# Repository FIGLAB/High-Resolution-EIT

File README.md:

# High-Resolution-EIT

The high resolution Electrical Impedance Tomograph (EIT) project is provided for academic and non-commercial research. This project is based on our publication at ACM UIST 2016: https://dl.acm.org/doi/abs/10.1145/2984511.2984574

## ACM Ref

Yang Zhang, Robert Xiao, and Chris Harrison. 2016. Advancing Hand Gesture Recognition with High Resolution Electrical Impedance Tomography. In Proceedings of the 29th Annual Symposium on User Interface Software and Technology (UIST '16). Association for Computing Machinery, New York, NY, USA, 843–850. DOI:https://doi.org/10.1145/2984511.2984574

## BibTex

```
@inproceedings{10.1145/2984511.2984574,
author = {Zhang, Yang and Xiao, Robert and Harrison, Chris},
title = {Advancing Hand Gesture Recognition with High Resolution Electrical Impedance Tomography},
year = {2016},
isbn = {9781450341899},
publisher = {Association for Computing Machinery},
address = {New York, NY, USA},
url = {https://doi.org/10.1145/2984511.2984574},
doi = {10.1145/2984511.2984574},
abstract = {Electrical Impedance Tomography (EIT) was recently employed in the HCI domain to detect hand gestures using an instrumented smartwatch. This prior work demonstrated great promise for non-invasive, high accuracy recognition of gestures for interactive control. We introduce a new system that offers improved sampling speed and resolution. In turn, this enables superior interior reconstruction and gesture recognition. More importantly, we use our new system as a vehicle for experimentation ' we compare two EIT sensing methods and three different electrode resolutions. Results from in-depth empirical evaluations and a user study shed light on the future feasibility of EIT for sensing human input.},
booktitle = {Proceedings of the 29th Annual Symposium on User Interface Software and Technology},
pages = {843–850},
numpages = {8},
keywords = {hand gestures, eit, electrical impedance tomography, biometrics, smartwatch, bio-impedance, input},
location = {Tokyo, Japan},
series = {UIST '16}
}
```

## Contact

For interests in commercialization, please reach out to CMU CTTEC for details at innovation@cmu.edu

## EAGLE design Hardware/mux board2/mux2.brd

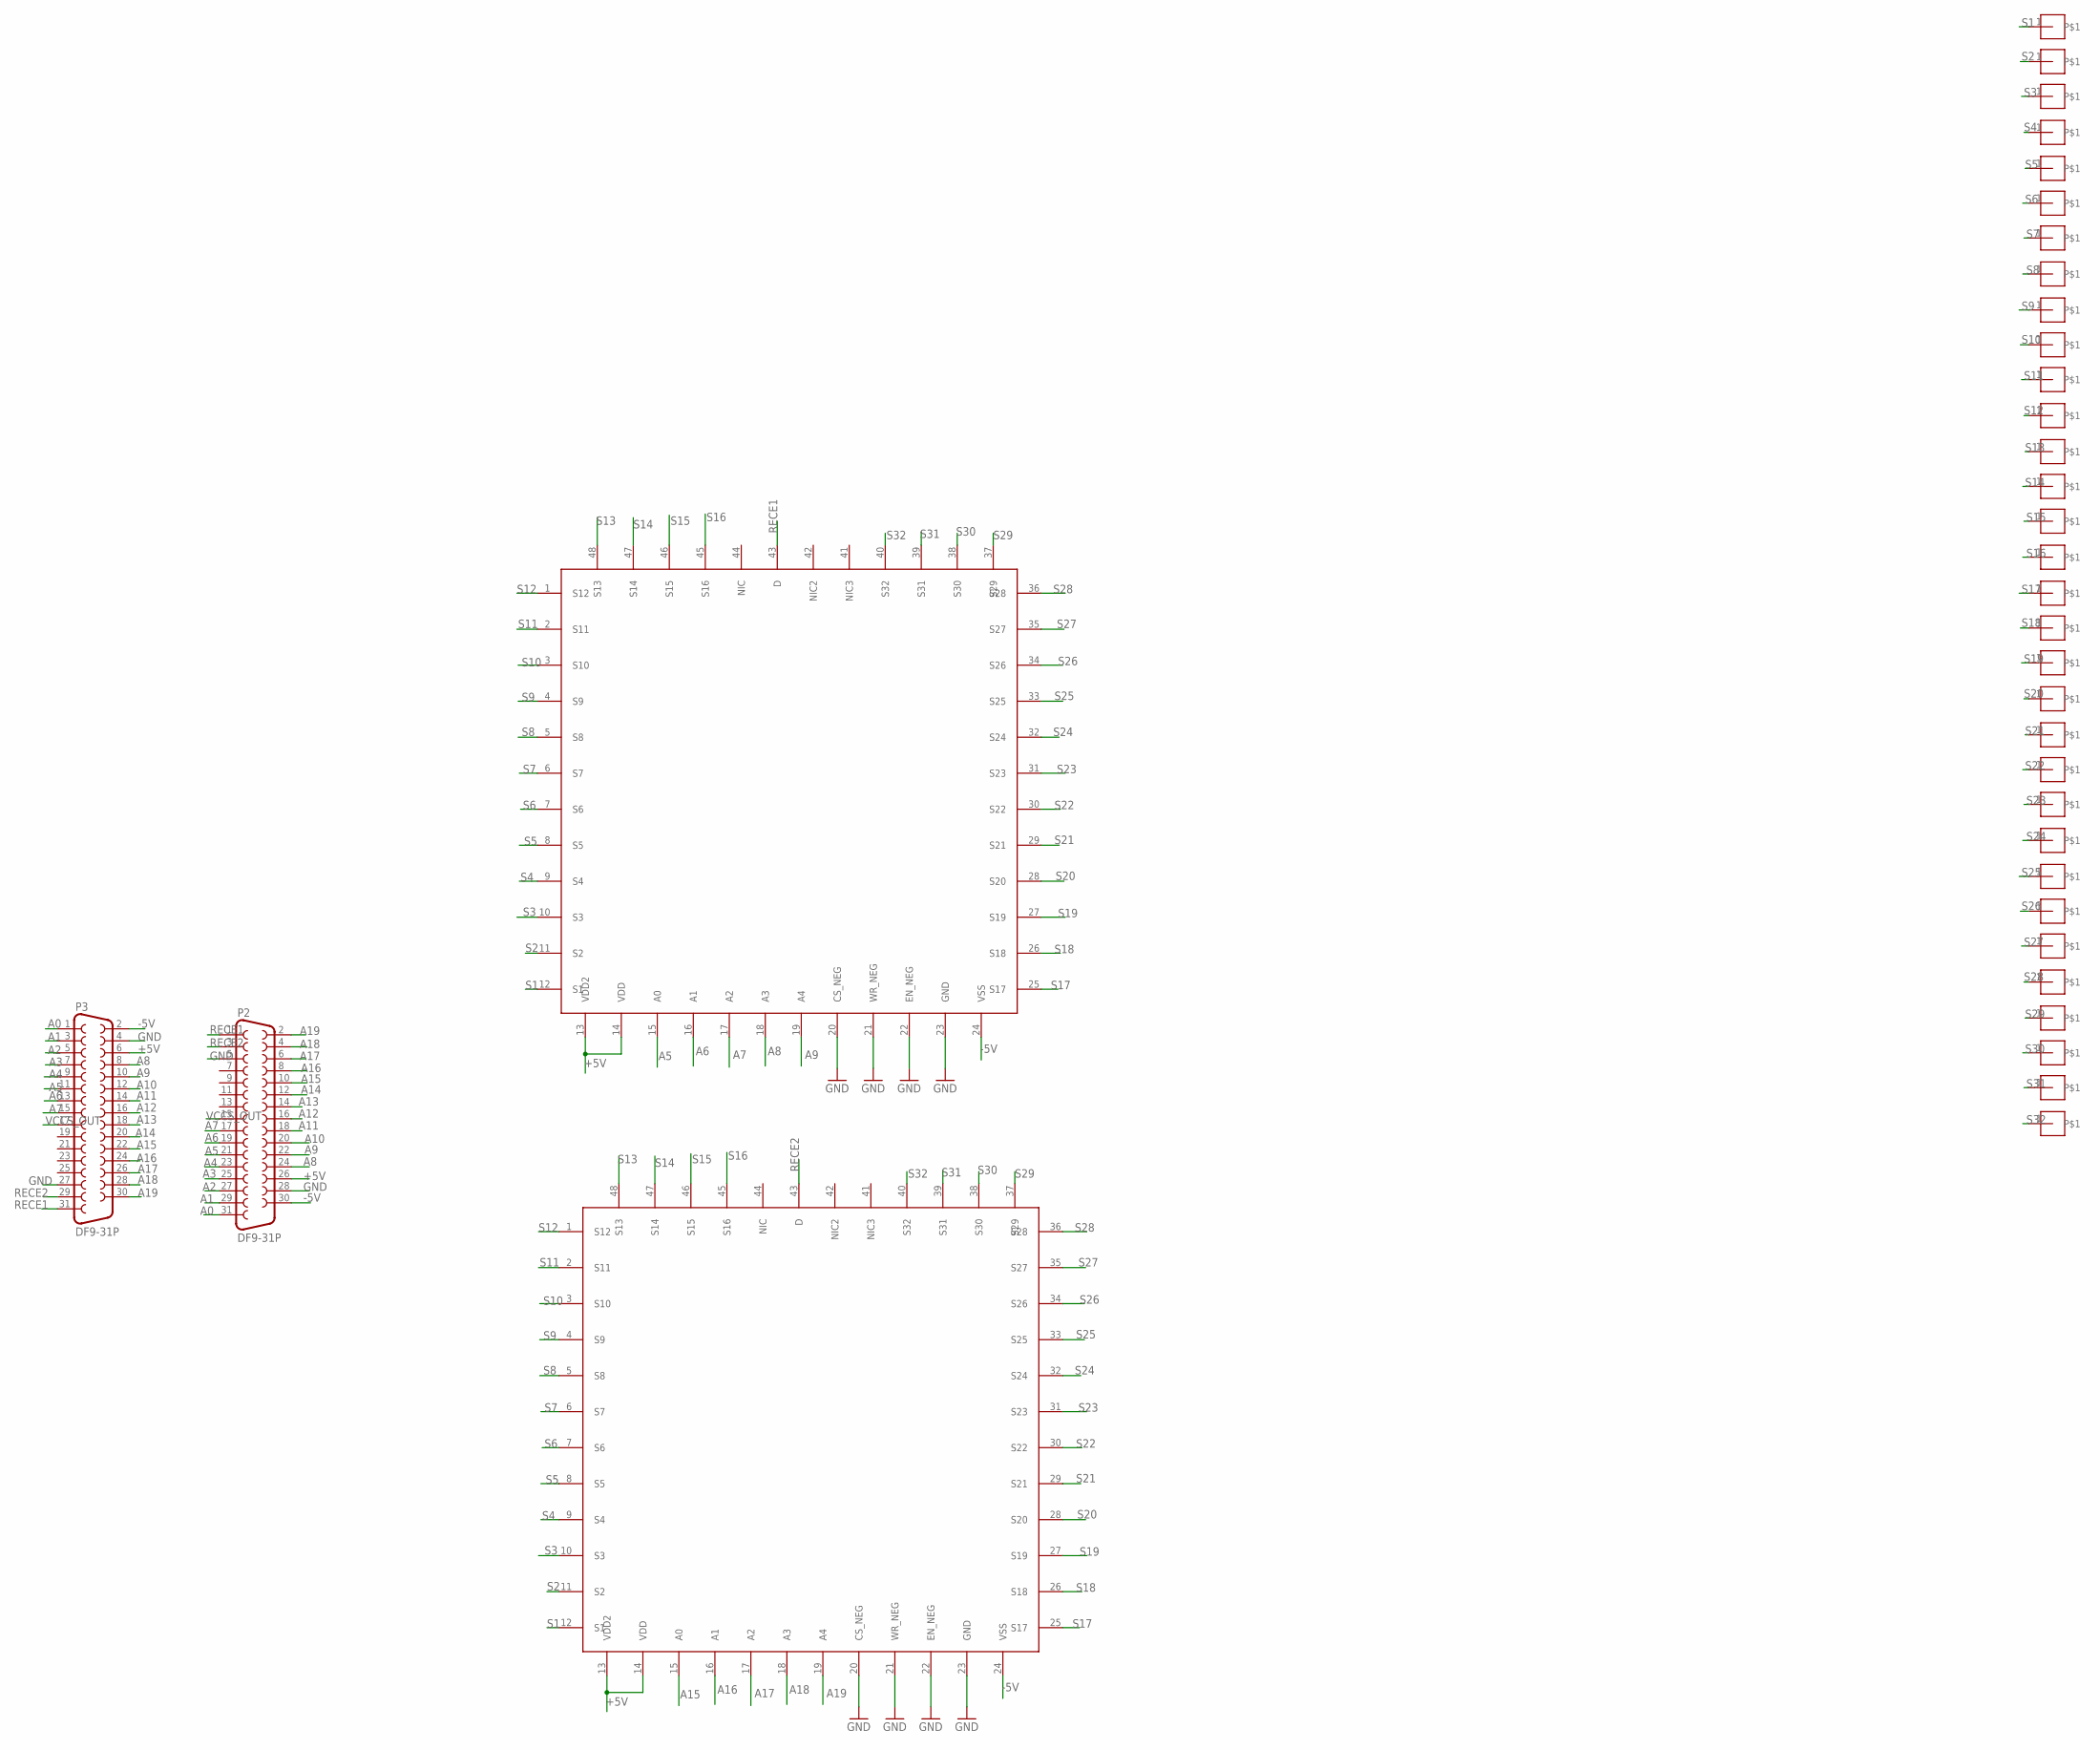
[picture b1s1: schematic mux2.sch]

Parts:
P2, P3: DF9-31P
U$25, U$26, U$27, U$28, U$29, U$30, U$31, U$32, U$33, U$34, U$35, U$36, U$37, U$38, U$39, U$40, U$41, U$42, U$43, U$44, U$45, U$46, U$47, U$48, U$49, U$50, U$51, U$52, U$53, U$54, U$55, U$56: M01
U$73, U$74: ADG732; TQFP48

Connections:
+5V: P2.26, P3.6, U$73.13 (VDD2), U$73.14 (VDD), U$74.13 (VDD2), U$74.14 (VDD)
-5V: P2.30, P3.2, U$73.24 (VSS), U$74.24 (VSS)
A0: P2.31, P3.1
A1: P2.29, P3.3
A2: P2.27, P3.5
A3: P2.25, P3.7
A4: P2.23, P3.9
A5: P2.21, P3.11, U$74.15 (A0)
A6: P2.19, P3.13, U$74.16 (A1)
A7: P2.17, P3.15, U$74.17 (A2)
A8: P2.24, P3.8, U$74.18 (A3)
A9: P2.22, P3.10, U$74.19 (A4)
A10: P2.20, P3.12
A11: P2.18, P3.14
A12: P2.16, P3.16
A13: P2.14, P3.18
A14: P2.12, P3.20
A15: P2.10, P3.22, U$73.15 (A0)
A16: P2.8, P3.24, U$73.16 (A1)
A17: P2.6, P3.26, U$73.17 (A2)
A18: P2.4, P3.28, U$73.18 (A3)
A19: P2.2, P3.30, U$73.19 (A4)
GND: P2.5, P2.28, P3.4, P3.27, U$73.20 (CS_NEG), U$73.21 (WR_NEG), U$73.22 (EN_NEG), U$73.23 (GND), U$74.20 (CS_NEG), U$74.21 (WR_NEG), U$74.22 (EN_NEG), U$74.23 (GND)
RECE1: P2.1, P3.31, U$74.43 (D)
RECE2: P2.3, P3.29, U$73.43 (D)
S1: U$25.1, U$73.12 (S1), U$74.12 (S1)
S2: U$26.1, U$73.11 (S2), U$74.11 (S2)
S3: U$27.1, U$73.10 (S3), U$74.10 (S3)
S4: U$28.1, U$73.9 (S4), U$74.9 (S4)
S5: U$29.1, U$73.8 (S5), U$74.8 (S5)
S6: U$30.1, U$73.7 (S6), U$74.7 (S6)
S7: U$31.1, U$73.6 (S7), U$74.6 (S7)
S8: U$32.1, U$73.5 (S8), U$74.5 (S8)
S9: U$33.1, U$73.4 (S9), U$74.4 (S9)
S10: U$34.1, U$73.3 (S10), U$74.3 (S10)
S11: U$35.1, U$73.2 (S11), U$74.2 (S11)
S12: U$36.1, U$73.1 (S12), U$74.1 (S12)
S13: U$37.1, U$73.48 (S13), U$74.48 (S13)
S14: U$38.1, U$73.47 (S14), U$74.47 (S14)
S15: U$39.1, U$73.46 (S15), U$74.46 (S15)
S16: U$40.1, U$73.45 (S16), U$74.45 (S16)
S17: U$41.1, U$73.25 (S17), U$74.25 (S17)
S18: U$42.1, U$73.26 (S18), U$74.26 (S18)
S19: U$43.1, U$73.27 (S19), U$74.27 (S19)
S20: U$44.1, U$73.28 (S20), U$74.28 (S20)
S21: U$45.1, U$73.29 (S21), U$74.29 (S21)
S22: U$46.1, U$73.30 (S22), U$74.30 (S22)
S23: U$47.1, U$73.31 (S23), U$74.31 (S23)
S24: U$48.1, U$73.32 (S24), U$74.32 (S24)
S25: U$49.1, U$73.33 (S25), U$74.33 (S25)
S26: U$50.1, U$73.34 (S26), U$74.34 (S26)
S27: U$51.1, U$73.35 (S27), U$74.35 (S27)
S28: U$52.1, U$73.36 (S28), U$74.36 (S28)
S29: U$53.1, U$73.37 (S29), U$74.37 (S29)
S30: U$54.1, U$73.38 (S30), U$74.38 (S30)
S31: U$55.1, U$73.39 (S31), U$74.39 (S31)
S32: U$56.1, U$73.40 (S32), U$74.40 (S32)
VCCS_OUT: P2.15, P3.17

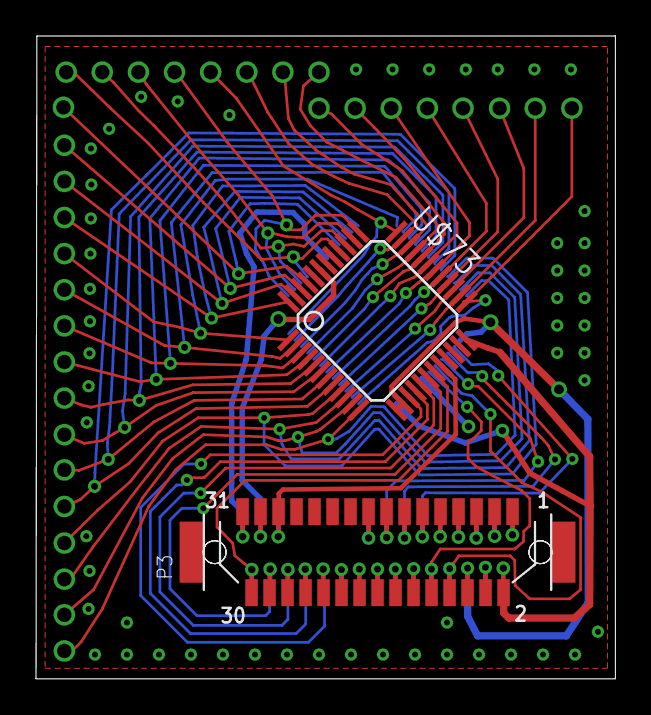
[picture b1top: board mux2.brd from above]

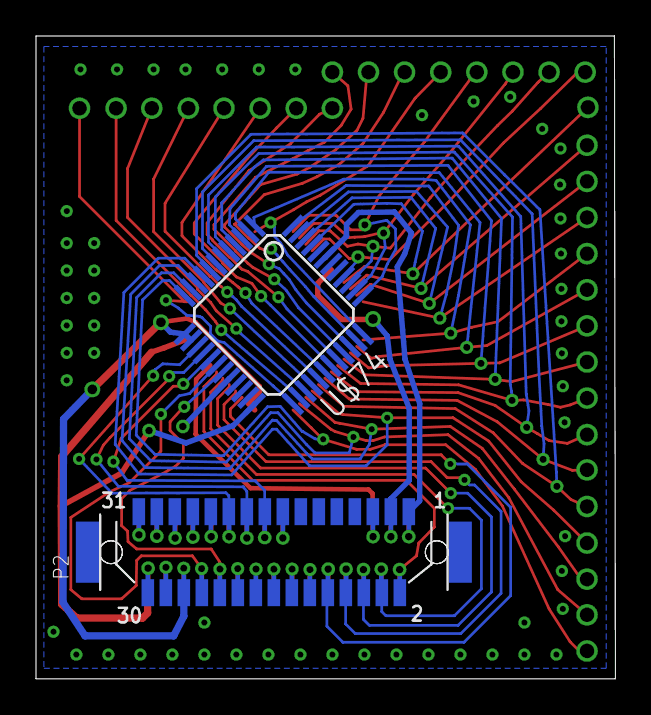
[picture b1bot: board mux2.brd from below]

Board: 2 copper layers, 32.2 x 35.7 mm, 36 parts (2 on the bottom side), 58 nets.

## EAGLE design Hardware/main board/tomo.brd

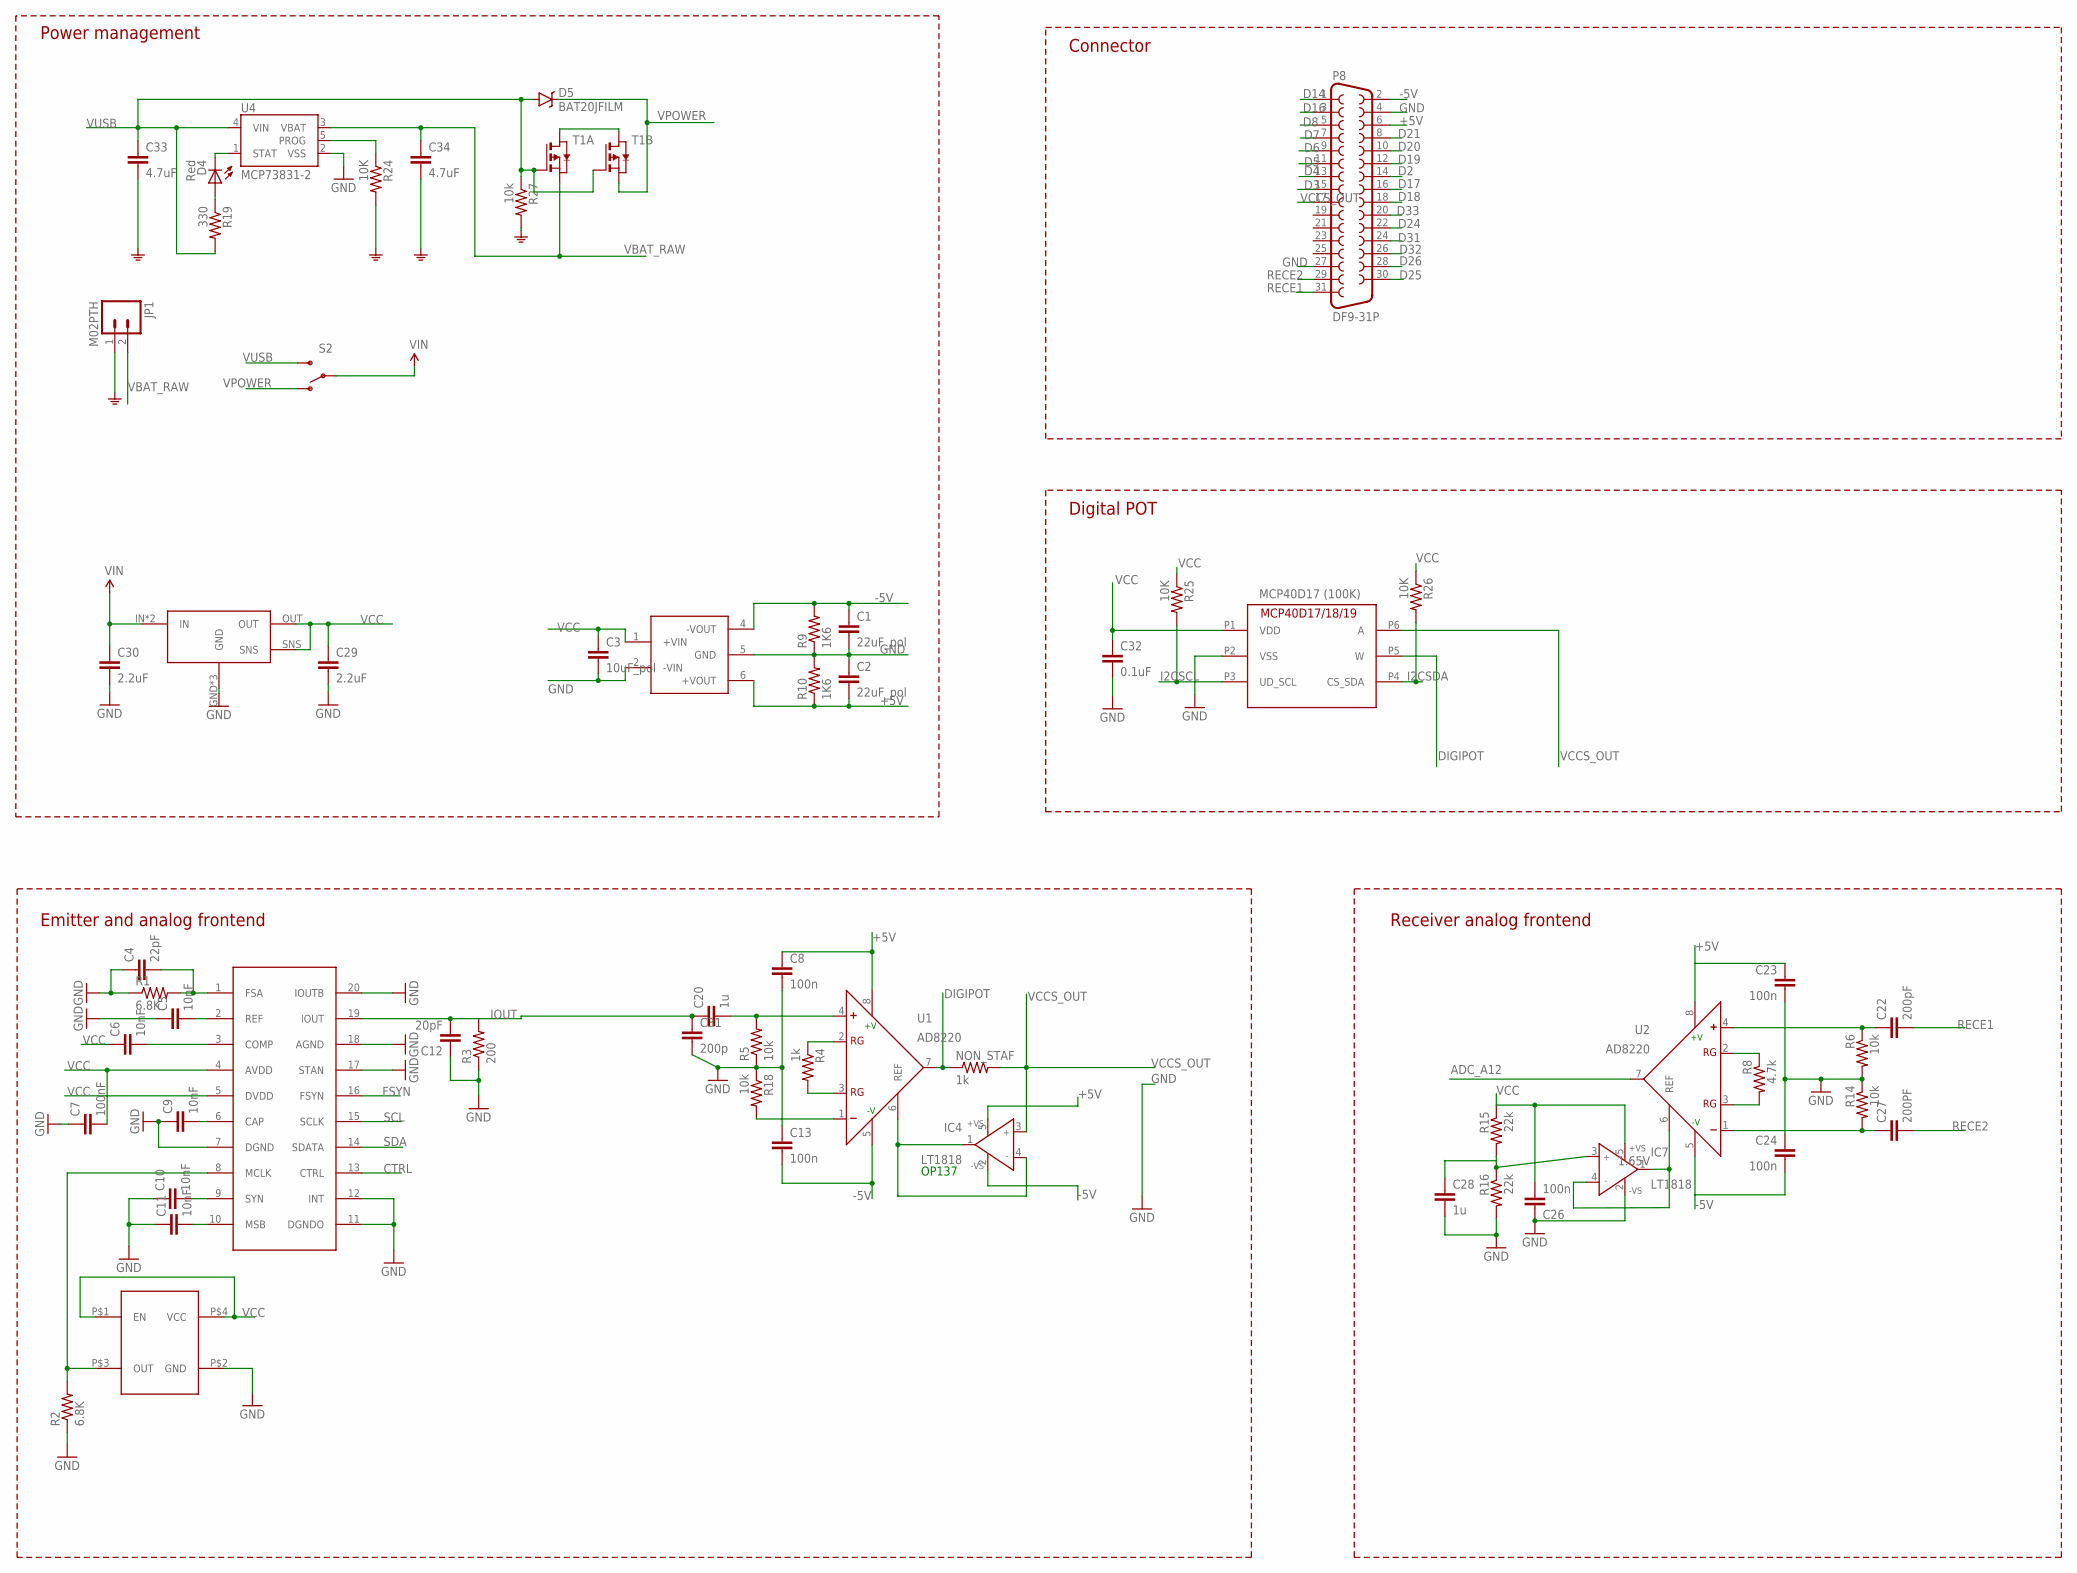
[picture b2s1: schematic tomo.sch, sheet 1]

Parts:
C1, C2: 22uF_pol; 0603-CAP
C3: 10uF_pol; 0603-CAP
C4: 22pF; 0603-CAP
C5, C6, C9, C10, C11: 10nF; 0603-CAP
C7: 100nF; 0603-CAP
C8, C13, C23, C24, C26: 100n; 0603-CAP
C12: 20pF; 0603-CAP
C20, C28: 1u; 0603-CAP
C22: 200pF; 0603-CAP
C27: 200PF; 0603-CAP
C29, C30: 2.2uF; 0402-CAP
C31: 200p; 0603-CAP
C32: 0.1uF; 0402-CAP
C33, C34: 4.7uF; 0402-CAP
D4: Red; LED-0603
D5: BAT20JFILM; SOD-323
IC4, IC7: LT1818; SOT23-5
JP1: M02PTH; 1X02
LP1: LP38691SD; WSON_6
NON_STAF: 1k; 0603-RES
P8: DF9-31P
R1, R2: 6.8K; 0603
R3: 200; 0603
R4: 1k; 0603-RES
R5, R18: 10k; 0603-RES
R6, R14: 10k; 0603
R8: 4.7k; 0603
R9, R10: 1K6; 0603-RES
R15, R16: 22k; 0603
R19: 330; 0402-RES
R24, R25, R26: 10K; 0402-RES
R27: 10k; 0402-RES
S2: SWITCH-SPDT-SMD-A; SWITCH-SPST-SMD-A
T1: BSS84DW; SOT363
U1, U2: AD8220; MSOP8
U4: MCP73831-2; SOT23-5
U$2: AD5930; TSSOP-20
U$3: OSC
U$4: DCDC_CONVERTOR
U$6: MCP40D17/18/19; SC70-6

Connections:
1.65V: IC7.1 (OUT), IC7.4 (IN-), U2.6 (REF)
+5V: C2.2, C8.1, C23.1, IC4.5 (+VS), P8.6, R10.1, U1.8 (+V), U2.8 (+V), U$4.6 (+VOUT)
-5V: C1.1, C13.2, C24.2, IC4.2 (-VS), P8.2, R9.2, U1.5 (-V), U2.5 (-V), U$4.4 (-VOUT)
ADC_A12: U2.7 (OUT); also elsewhere on the board
CTRL: U$2.13 (CTRL); also elsewhere on the board
D2: P8.14; also elsewhere on the board
D3: P8.15; also elsewhere on the board
D4: P8.13; also elsewhere on the board
D5: P8.11; also elsewhere on the board
D6: P8.9; also elsewhere on the board
D7: P8.7; also elsewhere on the board
D8: P8.5; also elsewhere on the board
D14: P8.1; also elsewhere on the board
D16: P8.3; also elsewhere on the board
D17: P8.16; also elsewhere on the board
D18: P8.18; also elsewhere on the board
D19: P8.12; also elsewhere on the board
D20: P8.10; also elsewhere on the board
D21: P8.8; also elsewhere on the board
D24: P8.22; also elsewhere on the board
D25: P8.30; also elsewhere on the board
D26: P8.28; also elsewhere on the board
D31: P8.24; also elsewhere on the board
D32: P8.26; also elsewhere on the board
D33: P8.20; also elsewhere on the board
DIGIPOT: NON_STAF.1, U1.7 (OUT), U$6.P5 (W)
FSYN: U$2.16 (FSYN); also elsewhere on the board
GND: C1.2, C2.1, C3.2, C4.1, C5.1, C7.1, C8.2, C9.1, C10.1, C11.1, C12.1, C13.1, C23.2, C24.1, C26.1, C28.2, C29.2, C30.2, C31.2, C32.2, C33.2, C34.2, IC7.2 (-VS), JP1.1, LP1.GND, LP1.N/C (GND), LP1.THERMAL (GND), P8.4, P8.27, R1.1, R2.1, R3.1, R5.1, R6.2, R9.1, R10.2, R14.1, R16.2, R18.1, R24.2, R27.2, U4.2 (VSS), U$2.7 (DGND), U$2.11 (DGNDO), U$2.12 (INT), U$2.17 (STAN), U$2.18 (AGND), U$2.20 (IOUTB), U$3.P$2 (GND), U$4.2 (-VIN), U$4.5 (GND), U$6.P2 (VSS); also elsewhere on the board
I2CSCL: R25.2, U$6.P3 (UD_SCL); also elsewhere on the board
I2CSDA: R26.2, U$6.P4 (CS_SDA); also elsewhere on the board
IOUT: C12.2, C20.1, C31.1, R3.2, U$2.19 (IOUT)
unnamed: C4.2, R1.2, U$2.1 (FSA)
unnamed: C6.2, U$2.3 (COMP)
unnamed: C5.2, U$2.2 (REF)
unnamed: C9.2, U$2.6 (CAP)
unnamed: R2.2, U$2.8 (MCLK), U$3.P$3 (OUT)
unnamed: C10.2, U$2.9 (SYN)
unnamed: C11.2, U$2.10 (MSB)
unnamed: R4.1, U1.2 (RG)
unnamed: C28.1, IC7.3 (IN+), R15.2, R16.1
unnamed: C20.2, R5.2, U1.4 (+)
unnamed: R4.2, U1.3 (RG)
unnamed: IC4.1 (OUT), IC4.4 (IN-), U1.6 (REF)
unnamed: R18.2, U1.1 (-)
unnamed: D4.A, R19.1
unnamed: T1.3 (D), T1.6 (D)
unnamed: C22.1, R6.1, U2.4 (+)
unnamed: C27.1, R14.2, U2.1 (-)
unnamed: R8.1, U2.2 (RG)
unnamed: R8.2, U2.3 (RG)
PROG: R24.1, U4.5 (PROG)
RECE1: C22.2, P8.31
RECE2: C27.2, P8.29
SCL: U$2.15 (SCLK); also elsewhere on the board
SDA: U$2.14 (SDATA); also elsewhere on the board
STAT: D4.C, U4.1 (STAT)
VBAT_RAW: C34.1, JP1.2, T1.4 (S), U4.3 (VBAT)
VCC: C3.1, C6.1, C7.2, C26.2, C29.1, C32.1, IC7.5 (+VS), LP1.OUT, LP1.SNS, R15.1, R25.1, R26.1, U$2.4 (AVDD), U$2.5 (DVDD), U$3.P$1 (EN), U$3.P$4 (VCC), U$4.1 (+VIN), U$6.P1 (VDD)
VCCS_OUT: IC4.3 (IN+), NON_STAF.2, P8.17, U$6.P6 (A)
VIN: C30.1, LP1.IN, LP1.IN2 (IN), S2.2; also elsewhere on the board
VPOWER: D5.C, S2.1 (O), T1.1 (S)
VUSB: C33.1, D5.A, R19.2, R27.1, S2.3 (S), T1.2 (G), T1.5 (G), U4.4 (VIN); also elsewhere on the board

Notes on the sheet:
OP137
MCP40D17 (100K)
Power management
Connector
Digital POT
Emitter and analog frontend
Receiver analog frontend

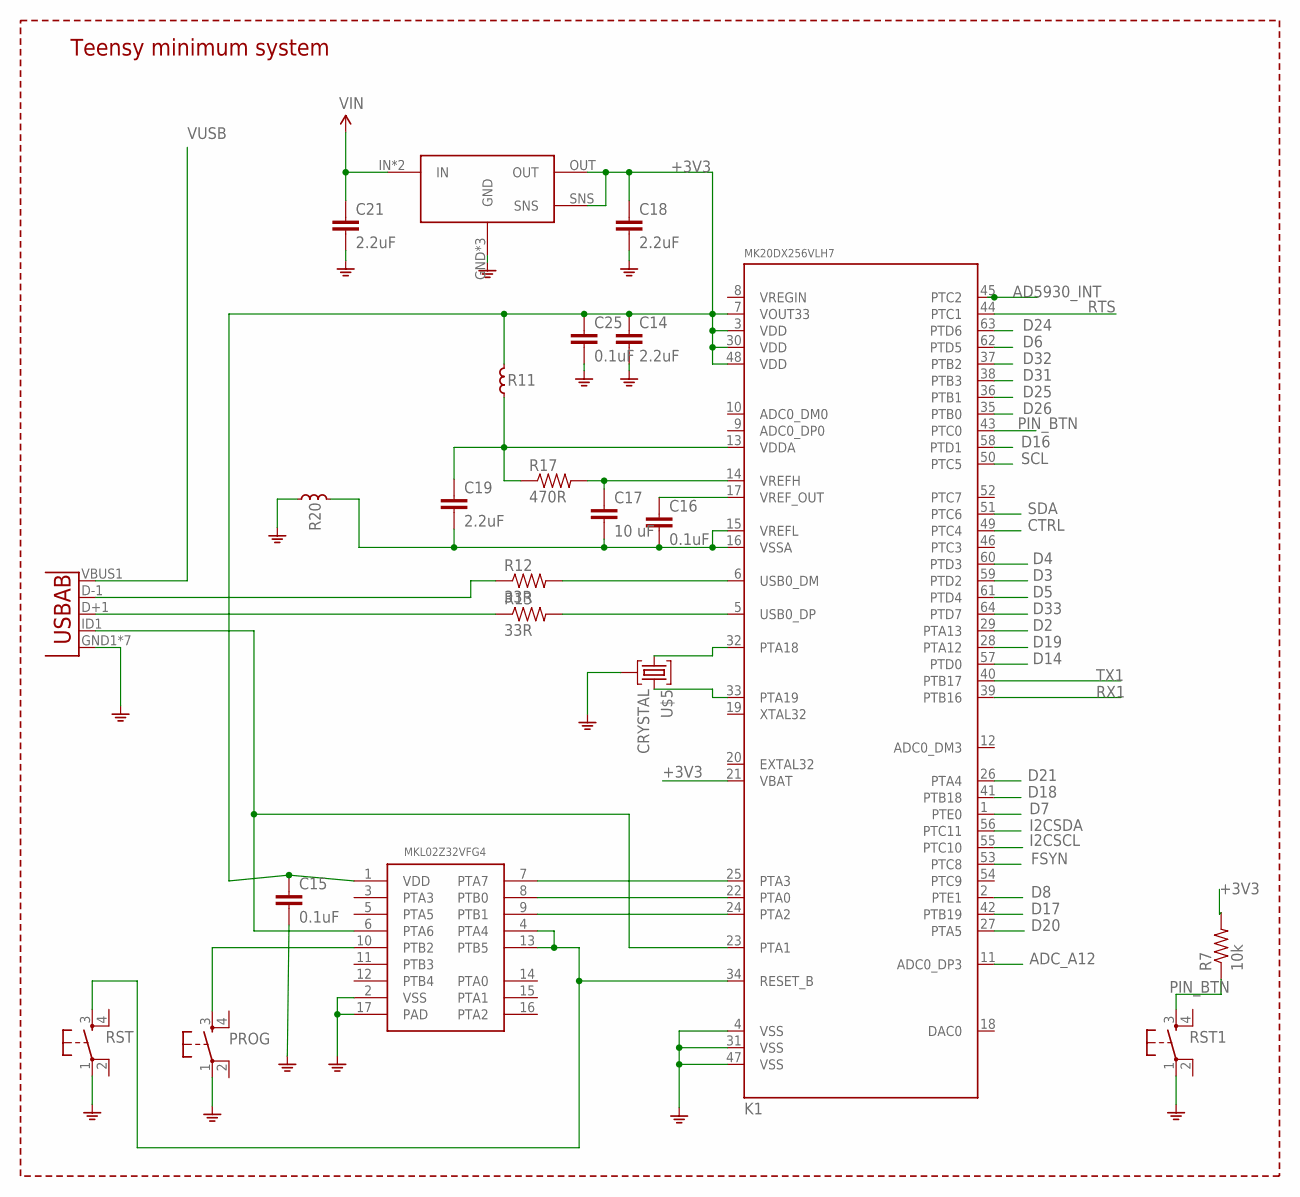
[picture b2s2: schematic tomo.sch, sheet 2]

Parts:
C14: 2.2uF; 0603-CAP
C15, C16, C25: 0.1uF; 0402-CAP
C17: 10 uF; 0402-CAP
C18, C19, C21: 2.2uF; 0402-CAP
K1: MK20DX256VLH7; LQFP64-05
LP38691: LP38691SD; WSON_6
PROG: KMR211GLFS; TACTILE_SWITCH_SMD
R7: 10k; 0402-RES
R11, R20: FERRITE; L0603
R12, R13: 33R; 0402-RES
R17: 470R; 0402-RES
RST, RST1: KMR211GLFS; TACTILE_SWITCH_SMD
U5: USB""; USB-MICRO-SMD
U$5: CRYSTAL
U$14: MKL02Z32VFG4_; QFN16_3X3

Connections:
+3V3: C14.1, C15.1, C18.1, C25.1, K1.3 (VDD), K1.7 (VOUT33), K1.21 (VBAT), K1.30 (VDD), K1.48 (VDD), LP38691.OUT, LP38691.SNS, R7.2, R11.2, U$14.1 (VDD); also elsewhere on the board
AD5930_INT: K1.45 (PTC2)
ADC_A12: K1.11 (ADC0_DP3); also elsewhere on the board
CTRL: K1.49 (PTC4); also elsewhere on the board
D2: K1.29 (PTA13); also elsewhere on the board
D3: K1.59 (PTD2); also elsewhere on the board
D4: K1.60 (PTD3); also elsewhere on the board
D5: K1.61 (PTD4); also elsewhere on the board
D6: K1.62 (PTD5); also elsewhere on the board
D7: K1.1 (PTE0); also elsewhere on the board
D8: K1.2 (PTE1); also elsewhere on the board
D14: K1.57 (PTD0); also elsewhere on the board
D16: K1.58 (PTD1); also elsewhere on the board
D17: K1.42 (PTB19); also elsewhere on the board
D18: K1.41 (PTB18); also elsewhere on the board
D19: K1.28 (PTA12); also elsewhere on the board
D20: K1.27 (PTA5); also elsewhere on the board
D21: K1.26 (PTA4); also elsewhere on the board
D24: K1.63 (PTD6); also elsewhere on the board
D25: K1.36 (PTB1); also elsewhere on the board
D26: K1.35 (PTB0); also elsewhere on the board
D31: K1.38 (PTB3); also elsewhere on the board
D32: K1.37 (PTB2); also elsewhere on the board
D33: K1.64 (PTD7); also elsewhere on the board
FSYN: K1.53 (PTC8); also elsewhere on the board
GND: C14.2, C15.2, C18.2, C21.2, C25.2, K1.4 (VSS), K1.31 (VSS), K1.47 (VSS), LP38691.GND, LP38691.N/C (GND), LP38691.THERMAL (GND), PROG.1, R20.1, RST.1, RST1.1, U5.GND1 (GND), U5.P$1 (GND), U5.P$2 (GND), U5.P$3 (GND), U5.P$4 (GND), U5.P$5 (GND), U5.P$6 (GND), U$5.GND1 (2), U$5.GND2 (2), U$14.2 (VSS), U$14.17 (PAD); also elsewhere on the board
I2CSCL: K1.55 (PTC10); also elsewhere on the board
I2CSDA: K1.56 (PTC11); also elsewhere on the board
unnamed: K1.24 (PTA2), U$14.9 (PTB1)
unnamed: K1.5 (USB0_DP), R13.2
unnamed: K1.6 (USB0_DM), R12.2
unnamed: R13.1, U5.D+1 (D+)
unnamed: C16.1, K1.17 (VREF_OUT)
unnamed: R12.1, U5.D-1 (D-)
unnamed: K1.23 (PTA1), U5.ID1 (USBID), U$14.6 (PTA6)
unnamed: K1.22 (PTA0), U$14.8 (PTB0)
unnamed: K1.32 (PTA18), U$5.SIG1 (1)
unnamed: K1.33 (PTA19), U$5.SIG2 (3)
unnamed: C17.1, K1.14 (VREFH), R17.2
unnamed: C16.2, C17.2, C19.2, K1.15 (VREFL), K1.16 (VSSA), R20.2
unnamed: C19.1, K1.13 (VDDA), R11.1, R17.1
unnamed: PROG.3, U$14.10 (PTB2)
unnamed: K1.25 (PTA3), U$14.7 (PTA7)
PIN_BTN: K1.43 (PTC0), R7.1, RST1.3
RST: K1.34 (RESET_B), RST.3, U$14.4 (PTA4), U$14.13 (PTB5)
RTS: K1.44 (PTC1); also elsewhere on the board
RX1: K1.39 (PTB16); also elsewhere on the board
SCL: K1.50 (PTC5); also elsewhere on the board
SDA: K1.51 (PTC6); also elsewhere on the board
TX1: K1.40 (PTB17); also elsewhere on the board
VIN: C21.1, LP38691.IN, LP38691.IN2 (IN); also elsewhere on the board
VUSB: U5.VBUS1 (VBUS); also elsewhere on the board

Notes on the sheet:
Teensy minimum system

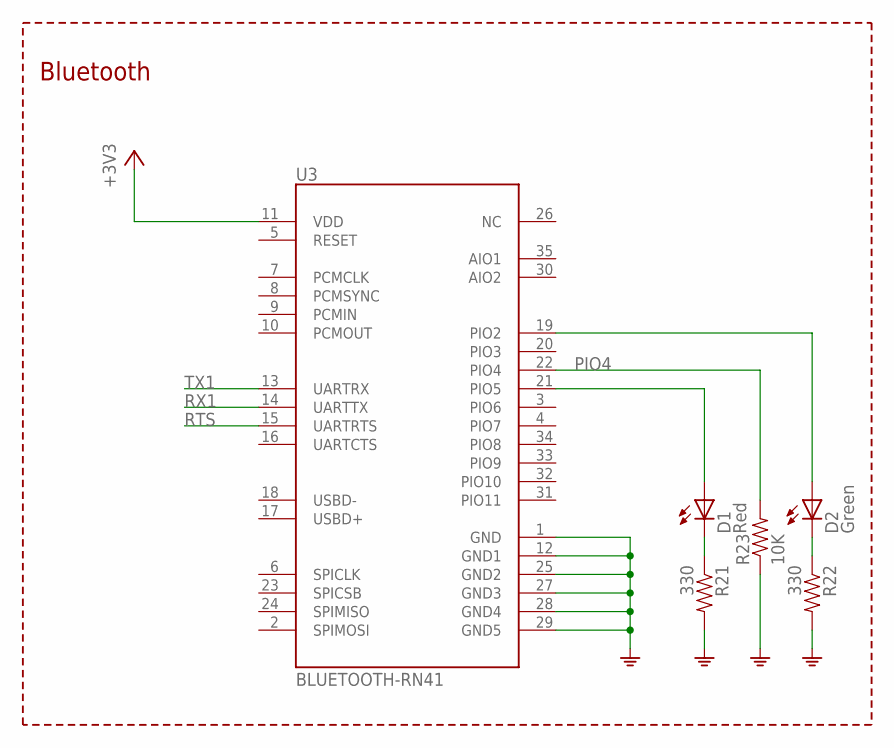
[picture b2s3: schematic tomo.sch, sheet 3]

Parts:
D1: Red; LED-0603
D2: Green; LED-0603
R21, R22: 330; 0402-RES
R23: 10K; 0402-RES
U3: BLUETOOTH-RN41; RN41

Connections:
+3V3: U3.11 (VDD); also elsewhere on the board
D1: D1.C, R21.1
D9: D2.C, R22.1
GND: R21.2, R22.2, R23.1, U3.1 (GND), U3.12 (GND1), U3.25 (GND2), U3.27 (GND3), U3.28 (GND4), U3.29 (GND5); also elsewhere on the board
unnamed: D1.A, U3.21 (PIO5)
unnamed: D2.A, U3.19 (PIO2)
PIO4: R23.2, U3.22 (PIO4)
RTS: U3.15 (UARTRTS); also elsewhere on the board
RX1: U3.14 (UARTTX); also elsewhere on the board
TX1: U3.13 (UARTRX); also elsewhere on the board

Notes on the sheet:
Bluetooth

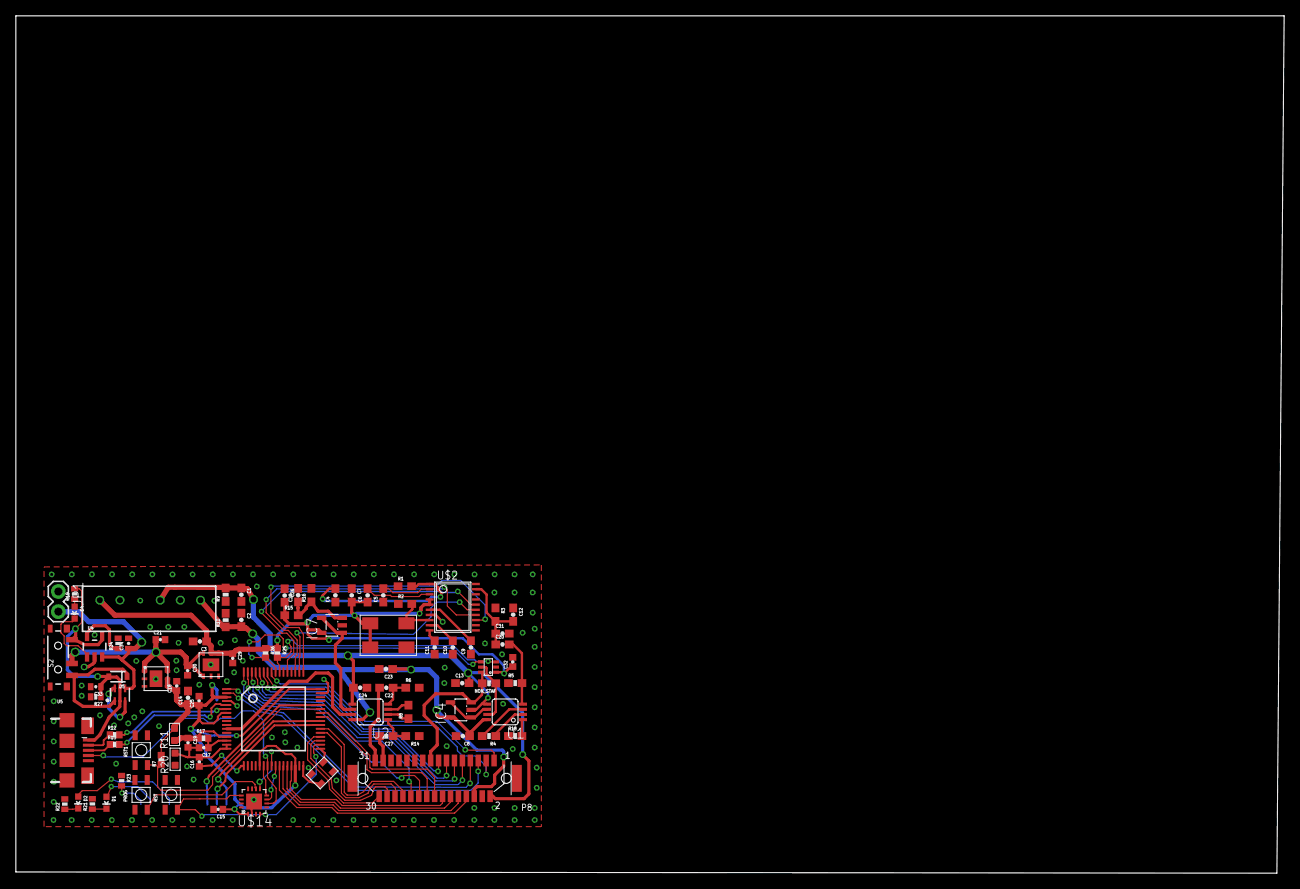
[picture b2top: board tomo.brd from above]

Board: 2 copper layers, 160.0 x 108.2 mm, 89 parts (1 on the bottom side), 88 nets.

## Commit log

2020-11-29 added readme
2020-11-29 added hardware design files
2020-11-29 formatted readme
2020-12-03 revised license files
2021-03-19 added firmware code
2021-03-19 added firmware readme

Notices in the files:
parts and their libraries:
SparkFun-Resistors: Licensing: Creative Commons ShareAlike 4.0 International - https://creativecommons.org/licenses/by-sa/4.0
